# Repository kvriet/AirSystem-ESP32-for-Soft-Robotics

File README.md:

# AirSystem for Soft Robotics
Modular Air System for Soft Robotics using ESP32\
Designed and created by [C.M. van Riet](https://research.tue.nl/en/persons/cm-katrien-van-riet) - Jan 2026\
With thanks to d.search at Eindhoven University of Technology for their guidance.\
Special thanks to Geert van den Boomen for checking the schematics and debugging the circuits.

## The system

**AirSystem-ESP32** was designed as a low-cost way to rapidly prototype with air, costing roughly €60 for the entire system. AirSystem consists of 1 controller, 4 pneumatic components (pumps and valves), and 2 pressure sensors. Through a 12V power brick, the board provides 12V power and as such, any pump or solenoid that requires 12V power can be attached to the board. 

### Pneumatic Components
For the pneumatic board, easy-to-find components are used:
1. Pump 370A, 12V, 3.2LPM
2. Solenoid valve Skoocom SC0829GW, 12V
3. MCP-H10 pressure sensor, 0-200kPa, 3.3V

### Manual
A manual for AirSystem describes in detail how the system works and how the Arduino library can be installed: [AirSystem Manual](https://github.com/kvriet/AirSystem-ESP32-for-Soft-Robotics/blob/main/Air%20System%20manual%20pcb%20v1.3.pdf)
Users are free to connect the sensor, pump, and valve to their inflatables as desired. Example Arduino sketches are provided that work well with the board to control inflatables.

## Arduino Library
The system is controlled by a Waveshare ESP32-C3-Zero and can be programmed through the Arduino IDE with a custom library: [AirSystem](https://github.com/kvriet/AirSystem-ESP32-for-Soft-Robotics/blob/main/AirSystem-ESP.zip) This folder should be unzipped and placed in the libraries folder of the Arduino folder, or imported (zipped) as a library in the Arduino IDE. Select the XIAO_ESP32C3 board to upload sketches to the board.

The library comes with 7 examples that showcase the abilities of **AirSystem**:
  1. Manual control
  2. Pressure reading
  3. Pump control
  4. Valve control
  5. Pump control without delay
  6. Other configurations
  7. Object arrays

## Schematics and KiCAD Files
The schematics for this project and the KiCAD files can be found here: [KiCAD folder](https://github.com/kvriet/AirSystem-for-Soft-Robotics/tree/main/KiCAD).

## 3D Printing Files
The STLs for this project can be found here: [Design Files](https://github.com/kvriet/AirSystem-ESP32-for-Soft-Robotics/tree/main/Design%20files).
- The prints will fit most regular printers and can be printed out of PLA, 0.3 layer height, 4 perimeters (walls), 20% infill. The cushions for the pumps and solenoids are printed in TPU. These cushions can be replaced with some sponge (simple kitchen sponges work well) if TPU printing is not an option.
- To minimise vibrations and prevent the cases from sliding around on a hard surface, 6mm silicone feet can be added to the bottom of the base.

The screws needed for these cases are:
- 4x M3x5 for the PCB 
- 12x M3x10 for the clamps (or 16x M3x10 depending on the configuration)

## Limitations
- The Skoocom solenoid valve is able to remain closed up to pressures of 100kPa, whereas the pump is able to deliver 150kPa. This means the valve will start leaking at pressures over 100kPa. In practice, this is not a major issue, as our projects rarely need pressures of over 100kPa (usually maxing out at 50kPa for haptic purposes). However, this overpressure might reduce valve longevity in the long run. In the future, a higher-pressure solenoid valve could be found, or a pump could be found that delivers max 100kPa. This would also allow for a lower-range pressure sensor to be used, the MCP-H10 0-100kPa, 3.3V. Switching to the 0-100kPa sensor would also double pressure measuring resolution.
- Currently no PID has been implemented in the library. As many inflatables or the tubing used are somewhat elastic, I have found that setting a target pressure (feedback loop sensor reading to pump power) is enough to achieve that pressure with a minimal offset. However, for more high-end applications, PID should be implemented.
- The Skoocom solenoid valve is not proportional. It is just open/closed. This means that controller deflation is a challenge. This can be worked around by turning on the pump simultaneously to opening the valve to reduce the air flowing out. Additionally, a resistor (very thin tube) could be connected to the valve outlet to reduce airflow out of the system. However, such a resistor also slows down response times when air does need to evacuate the system quickly. This is a trade-off for how cheap this entire system is.

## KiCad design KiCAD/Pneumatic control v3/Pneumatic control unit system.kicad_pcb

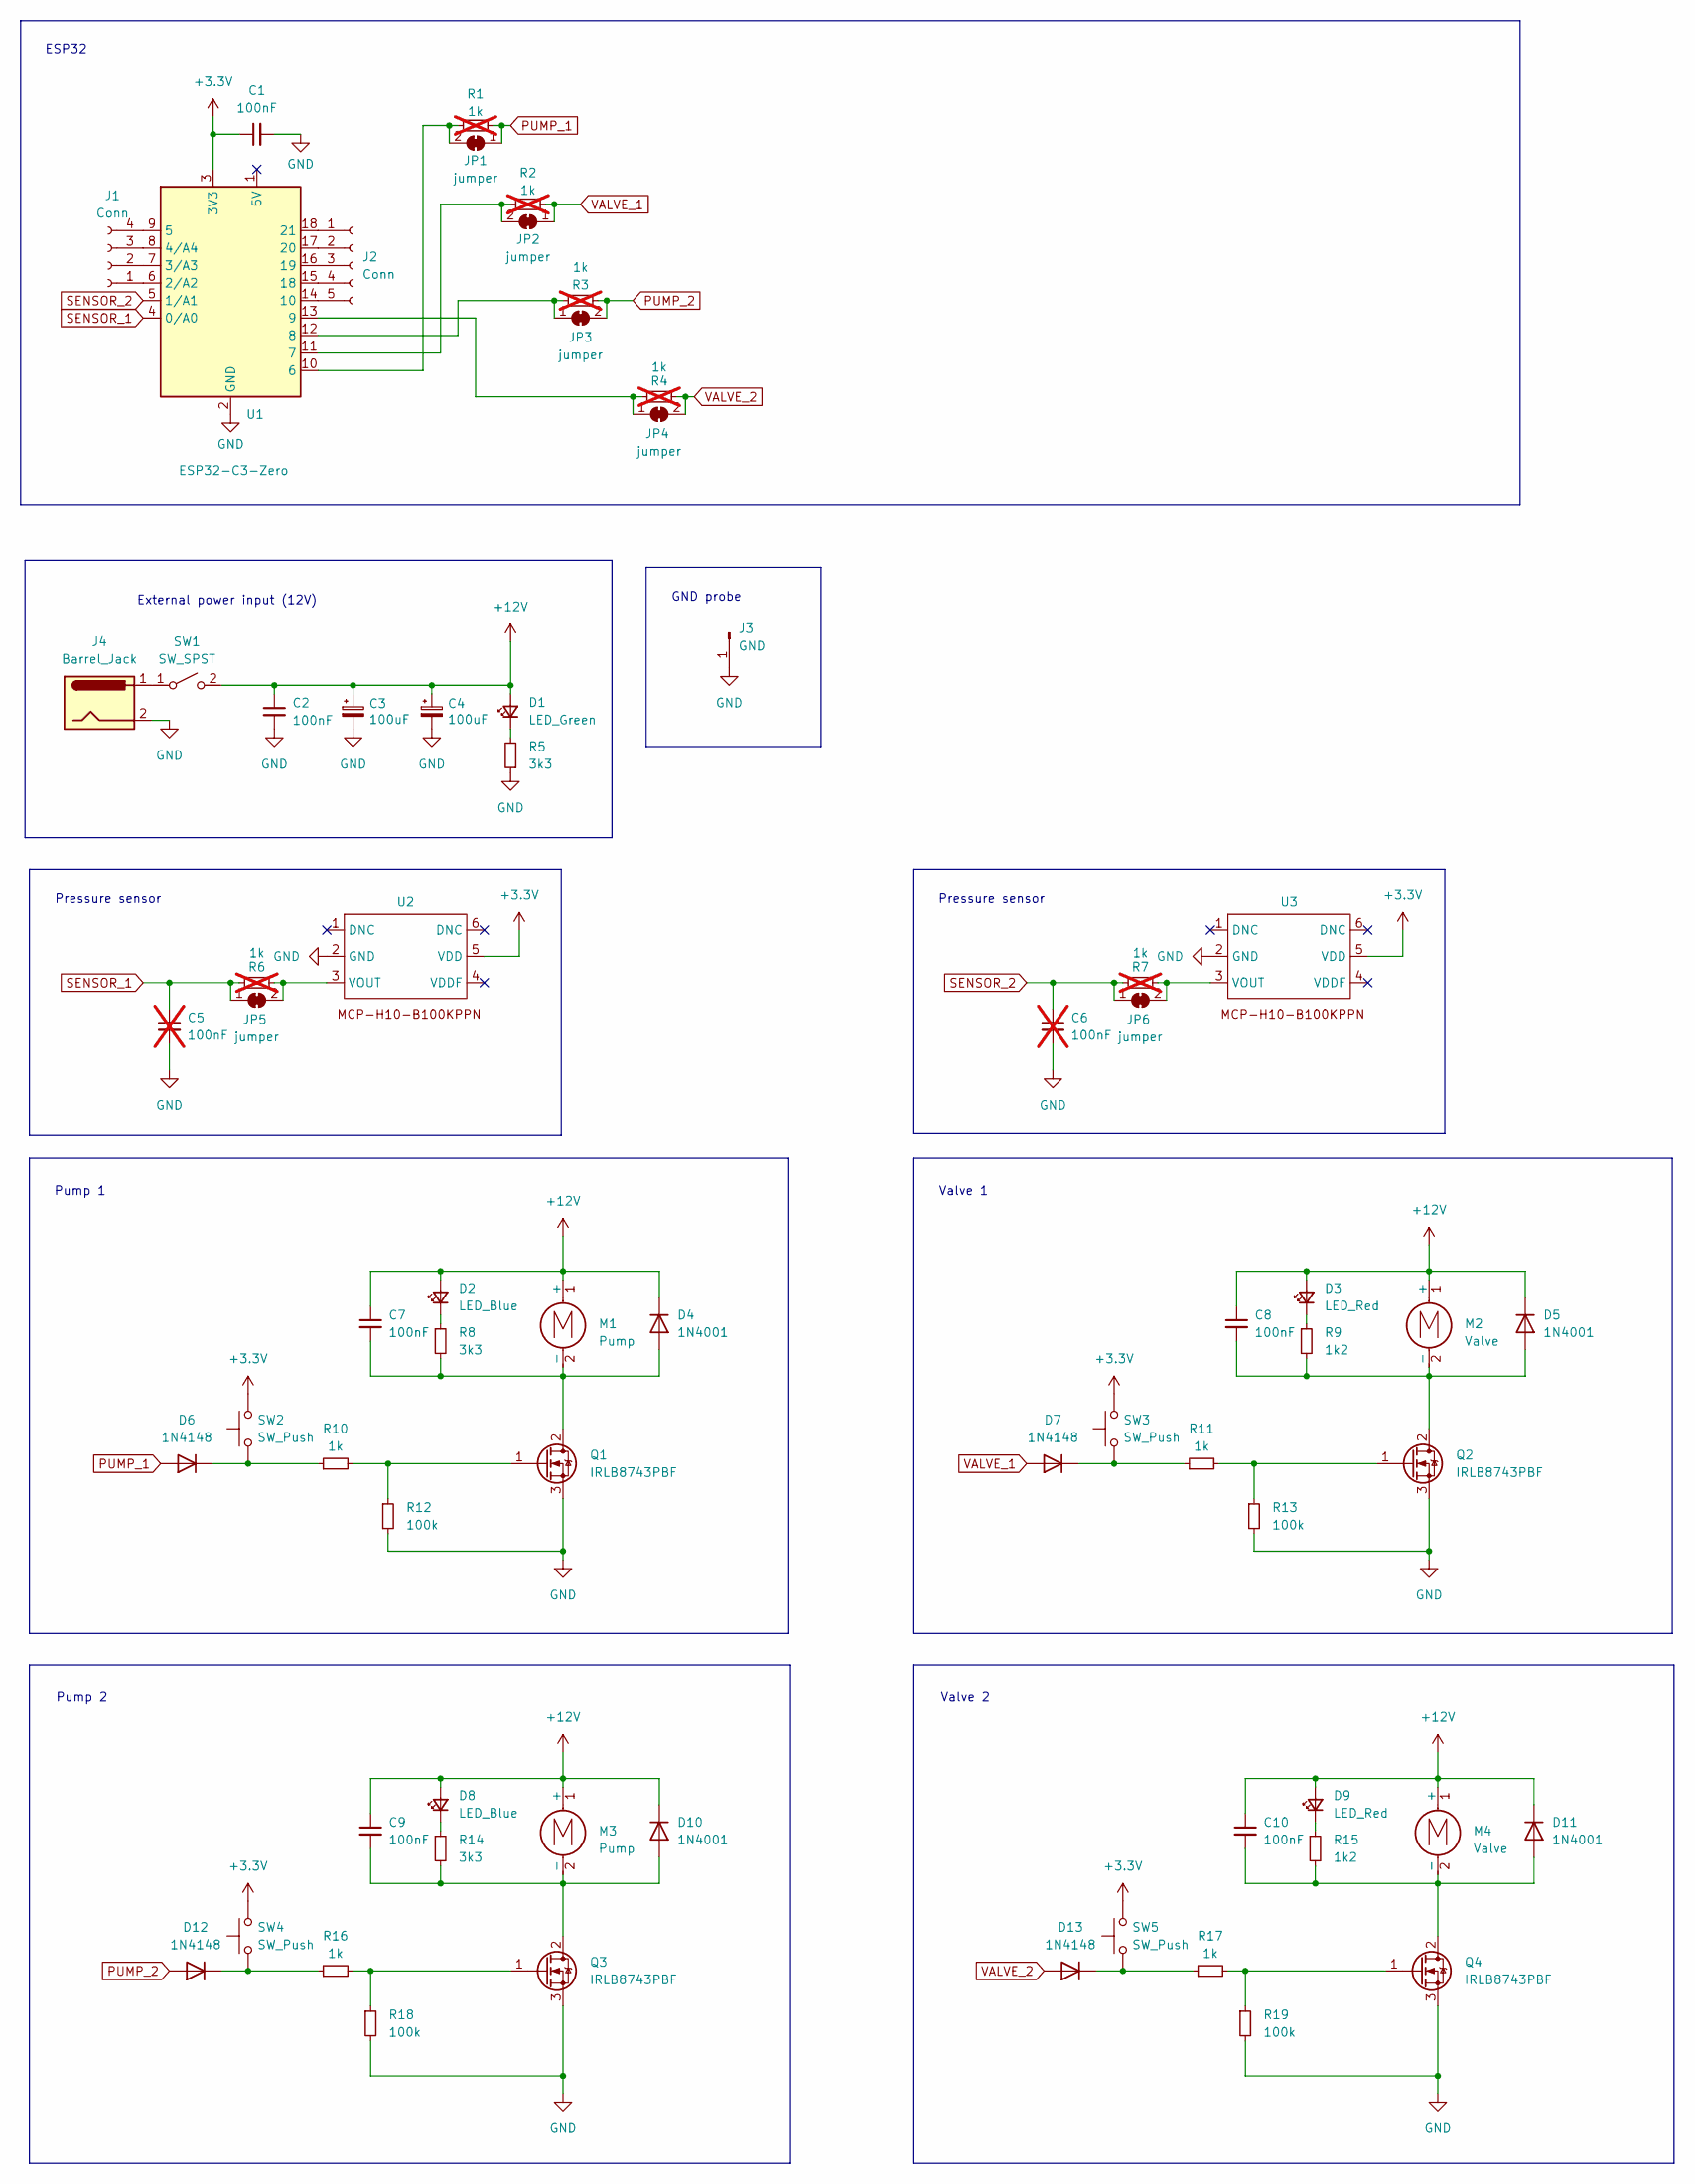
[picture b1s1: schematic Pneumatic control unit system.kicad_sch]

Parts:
C1, C2, C7, C8, C9, C10: 100nF; C_Rect_L7.2mm_W2.5mm_P5.00mm_FKS2_FKP2_MKS2_MKP2
C3, C4: 100uF; CP_Radial_D6.3mm_P2.50mm
C5, C6: 100nF; C_Rect_L7.2mm_W2.5mm_P5.00mm_FKS2_FKP2_MKS2_MKP2; not fitted
D1: LED_Green; LED_D3.0mm
D2, D8: LED_Blue; LED_D3.0mm
D3, D9: LED_Red; LED_D3.0mm
D4, D5, D10, D11: 1N4001; D_DO-41_SOD81_P10.16mm_Horizontal
D6, D7, D12, D13: 1N4148; D_DO-35_SOD27_P7.62mm_Horizontal
J1: Conn; PinSocket_1x04_P2.54mm_Vertical
J2: Conn; PinSocket_1x05_P2.54mm_Vertical
J3: GND; TestPoint_Loop_D2.50mm_Drill1.0mm
J4: Barrel_Jack; BarrelJack_Horizontal
JP1, JP2, JP3, JP4, JP5, JP6: jumper; SolderJumper-2_P1.3mm_Bridged_Pad1.0x1.5mm
M1, M3: Pump; TerminalBlock_Phoenix_MKDS-1,5-2_1x02_P5.00mm_Horizontal
M2, M4: Valve; TerminalBlock_Phoenix_MKDS-1,5-2_1x02_P5.00mm_Horizontal
Q1, Q2, Q3, Q4: IRLB8743PBF; TO-220-3_Vertical
R1, R2, R3, R4, R6, R7: 1k; R_Axial_DIN0207_L6.3mm_D2.5mm_P10.16mm_Horizontal; not fitted
R5, R8, R14: 3k3; R_Axial_DIN0207_L6.3mm_D2.5mm_P10.16mm_Horizontal
R9, R15: 1k2; R_Axial_DIN0207_L6.3mm_D2.5mm_P10.16mm_Horizontal
R10, R11, R16, R17: 1k; R_Axial_DIN0207_L6.3mm_D2.5mm_P10.16mm_Horizontal
R12, R13, R18, R19: 100k; R_Axial_DIN0207_L6.3mm_D2.5mm_P10.16mm_Horizontal
SW1: SW_SPST; SW_rocker_switch_small
SW2, SW3, SW4, SW5: SW_Push; SW_PUSH_6mm
U1: ESP32-C3-Zero
U2, U3: MCP_H10_breakout

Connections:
+3.3V: C1.1, SW2.2, SW3.2, SW4.2, SW5.2, U1.3 (3V3), U2.5 (VDD), U3.5 (VDD)
+12V: C2.1, C3.1, C4.1, C7.1, C8.1, C9.1, C10.1, D1.2 (A), D2.2 (A), D3.2 (A), D4.1 (K), D5.1 (K), D8.2 (A), D9.2 (A), D10.1 (K), D11.1 (K), M1.1 (+), M2.1 (+), M3.1 (+), M4.1 (+), SW1.2 (B)
GND: C1.2, C2.2, C3.2, C4.2, C5.2, C6.2, J3.1, J4.2, Q1.3 (S), Q2.3 (S), Q3.3 (S), Q4.3 (S), R5.1, R12.2, R13.2, R18.2, R19.2, U1.2 (GND), U2.2 (GND), U3.2 (GND); also elsewhere on the board
unnamed: D1.1 (K), R5.2
unnamed: D2.1 (K), R8.1
unnamed: D3.1 (K), R9.1
unnamed: C7.2, D4.2 (A), M1.2 (-), Q1.2 (D), R8.2
unnamed: C8.2, D5.2 (A), M2.2 (-), Q2.2 (D), R9.2
unnamed: D6.1 (K), R10.1, SW2.1
unnamed: D7.1 (K), R11.1, SW3.1
unnamed: D8.1 (K), R14.1
unnamed: D9.1 (K), R15.1
unnamed: C9.2, D10.2 (A), M3.2 (-), Q3.2 (D), R14.2
unnamed: C10.2, D11.2 (A), M4.2 (-), Q4.2 (D), R15.2
unnamed: D12.1 (K), R16.1, SW4.1
unnamed: D13.1 (K), R17.1, SW5.1
unnamed: J1.1, U1.6 (2/A2)
unnamed: J1.2, U1.7 (3/A3)
unnamed: J1.3, U1.8 (4/A4)
unnamed: J1.4, U1.9 (5)
unnamed: J2.1, U1.18 (21)
unnamed: J2.2, U1.17 (20)
unnamed: J2.3, U1.16 (19)
unnamed: J2.4, U1.15 (18)
unnamed: J2.5, U1.14 (10)
unnamed: JP1.2 (B), R1.1, U1.10 (6)
unnamed: JP2.2 (B), R2.1, U1.11 (7)
unnamed: JP3.1 (A), R3.2, U1.12 (8)
unnamed: JP4.1 (A), R4.2, U1.13 (9)
unnamed: JP5.2 (B), R6.1, U2.3 (VOUT)
unnamed: JP6.2 (B), R7.1, U3.3 (VOUT)
unnamed: Q1.1 (G), R10.2, R12.1
unnamed: Q2.1 (G), R11.2, R13.1
unnamed: Q3.1 (G), R16.2, R18.1
unnamed: Q4.1 (G), R17.2, R19.1
unnamed: J4.1, SW1.1 (A)
PUMP_1: D6.2 (A), JP1.1 (A), R1.2
PUMP_2: D12.2 (A), JP3.2 (B), R3.1
SENSOR_1: C5.1, JP5.1 (A), R6.2, U1.4 (0/A0)
SENSOR_2: C6.1, JP6.1 (A), R7.2, U1.5 (1/A1)
VALVE_1: D7.2 (A), JP2.1 (A), R2.2
VALVE_2: D13.2 (A), JP4.2 (B), R4.1

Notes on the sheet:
GND probe
Pressure sensor
Pump 2
External power input (12V)
Pump 1
Valve 1
ESP32
Valve 2

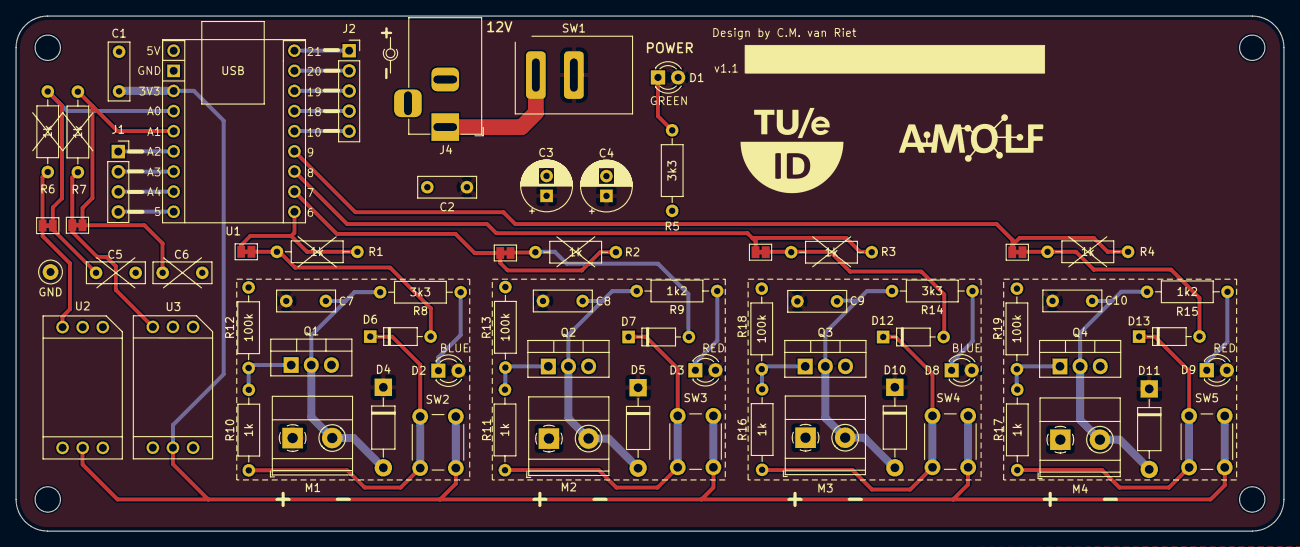
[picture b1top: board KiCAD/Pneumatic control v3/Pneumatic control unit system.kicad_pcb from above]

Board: 2 copper layers, 160.0 x 65.0 mm, 68 parts (0 on the bottom side), 42 nets.

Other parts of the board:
GND: GND; TestPoint_Loop_D2.50mm_Drill1.0mm

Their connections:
GND: GND.1; also elsewhere on the board

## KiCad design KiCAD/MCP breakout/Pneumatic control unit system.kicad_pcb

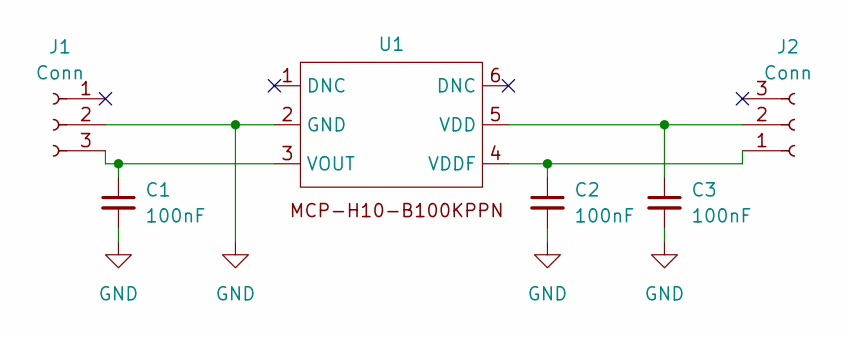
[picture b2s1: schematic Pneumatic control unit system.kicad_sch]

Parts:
C1, C2, C3: 100nF; C_0603_1608Metric_Pad1.08x0.95mm_HandSolder
J1, J2: Conn; PinHeader_1x03_P2.54mm_Vertical
U1: MCP-H10

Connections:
GND: C1.2, C2.2, C3.2, J1.2, U1.2 (GND)
unnamed: C1.1, J1.3, U1.3 (VOUT)
unnamed: C2.1, J2.1, U1.4 (VDDF)
unnamed: C3.1, J2.2, U1.5 (VDD)

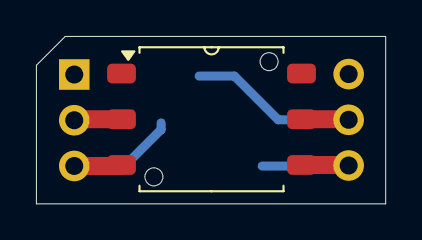
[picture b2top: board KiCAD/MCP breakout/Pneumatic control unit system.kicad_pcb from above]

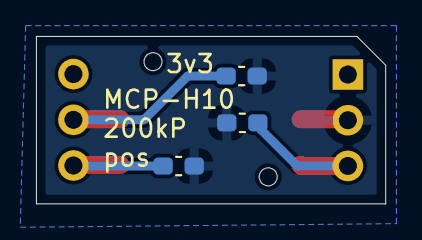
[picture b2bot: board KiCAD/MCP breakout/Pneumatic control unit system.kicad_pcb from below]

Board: 2 copper layers, 19.4 x 9.3 mm, 6 parts (5 on the bottom side), 4 nets.

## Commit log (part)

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2026-01-13 added manual and updated readme
2026-01-13 added library and photo
2026-01-13 added overview board
2026-01-13 Added KiCAD and design files
2026-01-13 Updated print files
2026-01-13 updated board overview pictures
2026-01-13 updated media
2026-01-13 deleted media
2026-01-23 corrected valve control
    digitalWrite changed to analogWrite
2026-01-23 updated manual
2026-01-23 updated sketches
2026-01-25 zipped library function
